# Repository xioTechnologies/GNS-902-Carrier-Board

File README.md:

GNS-902-Carrier-Board
=====================

Carrier board for the [GNS 902 GPS](http://www.gns-gmbh.com/index.php?id=271) module.  Includes CR2032 back up battery and LED to indicate fix status.  The header pinout is compatible with a 3.3V [FTDI device](https://www.sparkfun.com/products/9873).

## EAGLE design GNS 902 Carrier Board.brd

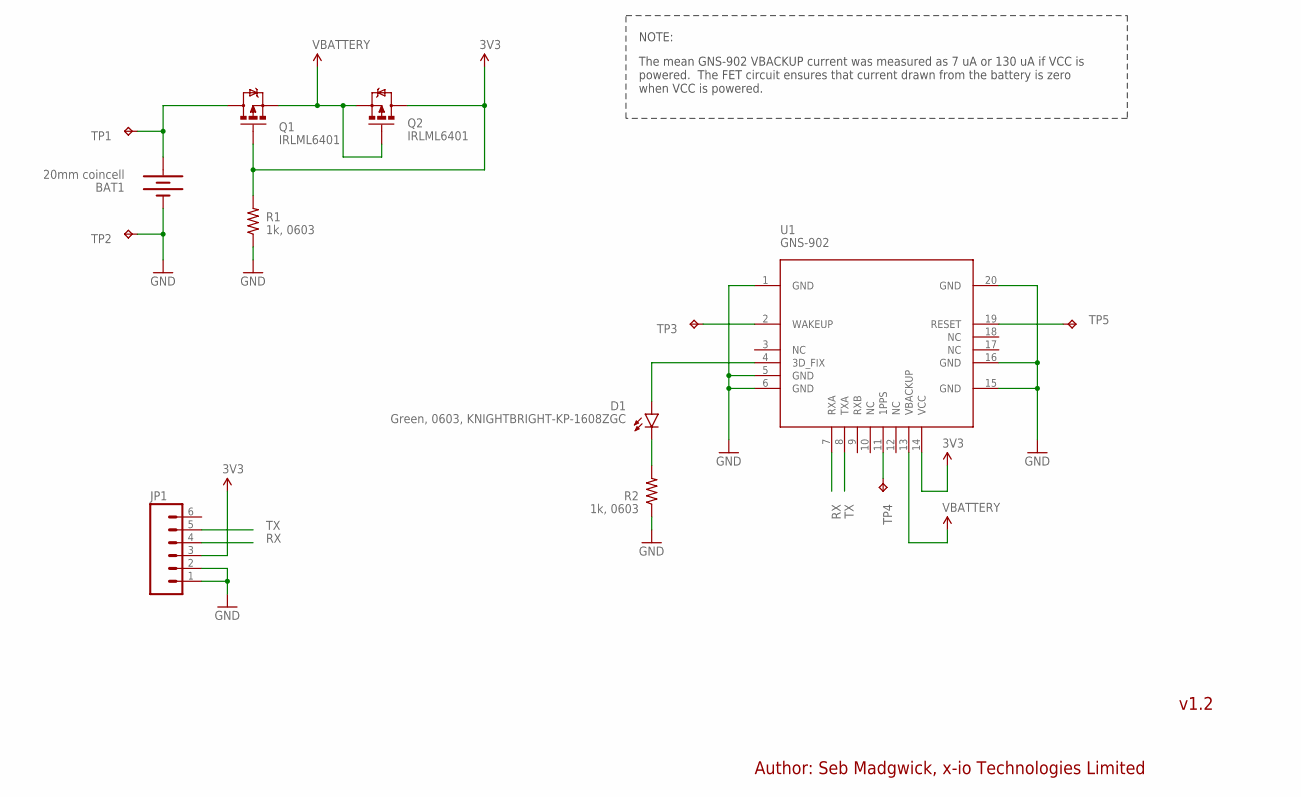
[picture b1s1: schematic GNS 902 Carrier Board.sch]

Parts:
BAT1: 20mm coincell; BATTCON_20MM_4LEGS
D1: Green, 0603, KNIGHTBRIGHT-KP-1608ZGC; LED-0603
JP1: M06NO_SILK_FEMALE_PTH; 1X06_NO_SILK
Q1, Q2: IRLML6401; SOT23-3
R1, R2: 1k, 0603; 0603-RES
TP1, TP2: TPTP15R; TP15R
TP3, TP4, TP5: TPTP10R; TP10R
U1: GNS-902

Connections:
3V3: JP1.3, Q1.1 (G), Q2.3 (D), R1.2, U1.14 (VCC)
GND: BAT1.2 (-), JP1.1, JP1.2, R1.1, R2.1, TP2.TP, U1.1 (GND), U1.5 (GND), U1.6 (GND), U1.15 (GND), U1.16 (GND), U1.20 (GND)
unnamed: D1.A, U1.4 (3D_FIX)
unnamed: D1.C, R2.2
unnamed: TP3.TP, U1.2 (WAKEUP)
unnamed: TP4.TP, U1.11 (1PPS)
unnamed: TP5.TP, U1.19 (RESET)
unnamed: BAT1.1 (+), Q1.3 (D), TP1.TP
RX: JP1.4, U1.7 (RXA)
TX: JP1.5, U1.8 (TXA)
VBATTERY: Q1.2 (S), Q2.1 (G), Q2.2 (S), U1.13 (VBACKUP)

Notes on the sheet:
v1.2
Author: Seb Madgwick, x-io Technologies Limited
The mean GNS-902 VBACKUP current was measured as 7 uA or 130 uA if VCC is powered. The FET circuit ensures that current drawn from the battery is zero when VCC is powered.
NOTE:

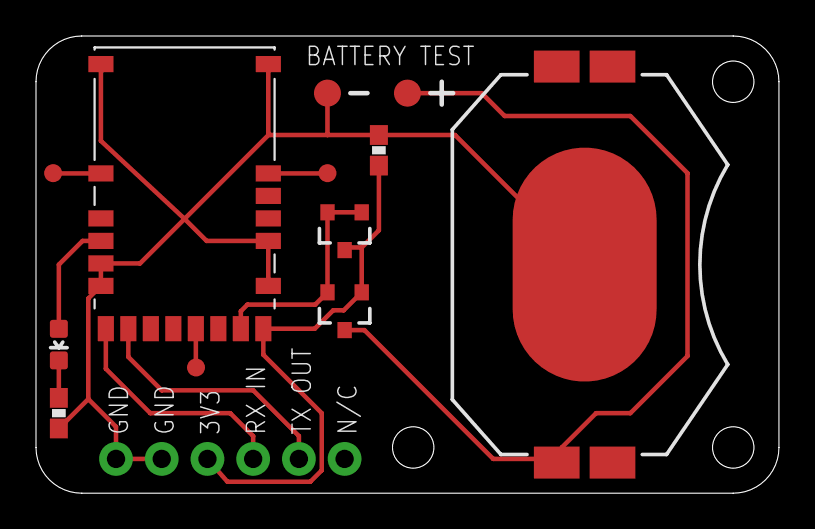
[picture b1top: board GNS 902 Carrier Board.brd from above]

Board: 2 copper layers, 41.3 x 25.4 mm, 13 parts (0 on the bottom side), 11 nets.

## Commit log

2015-09-14 Commit project files
2015-09-20 Add automatic VBACKUP power source switch
2015-10-01 Add photo of assembled PCB
2015-10-01 Correct GNS-902 footprint and add notes to schematic

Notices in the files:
parts and their libraries:
SparkFun-Resistors: Licensing: Creative Commons ShareAlike 4.0 International - https://creativecommons.org/licenses/by-sa/4.0
